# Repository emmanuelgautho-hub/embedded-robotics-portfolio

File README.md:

# embedded-robotics-portfolio
Portfolio de projets en Systèmes Embarqués, Robotique &amp; Vision IA - Emmanuel GAUTHO (ESIGELEC)
# Portfolio : Systèmes Embarqués et Robotique

Ce dépôt centralise mes principaux projets techniques et académiques. Je m'appelle Emmanuel Gautho, je suis actuellement étudiant en 2ème année de cycle ingénieur à l'ESIGELEC, spécialisé en Systèmes Embarqués. Mes travaux portent principalement sur la robotique mobile, le développement de micrologiciels (firmware) bas niveau et la vision par ordinateur.

## Projets

### Navigation de Robot Quadrupède (Deep Robotics Lite3 & ROS2)
Développement d'une stack de perception et de navigation autonome pour un robot quadrupède en environnement complexe.
* Conception et implémentation d'un système de détection d'escaliers basé sur une caméra Intel RealSense, OpenCV et YOLO.
* Traitement en temps réel des flux vidéo et de profondeur pour l'extraction des caractéristiques de l'environnement.
* Création de nœuds ROS2 personnalisés pour interfacer les données de vision avec le système de contrôle des moteurs du robot.

### Robot Mobile Autonome (MSP430)
Conception du firmware bare-metal pour un petit véhicule autonome focalisé sur l'évitement d'obstacles et le suivi de trajectoire.
* Interfaçage et traitement des signaux provenant de capteurs de distance à ultrasons.
* Gestion des actionneurs et des moteurs à courant continu via des signaux PWM et des interruptions matérielles.
* Optimisation du code C bas niveau pour fonctionner sous contraintes de ressources sur un microcontrôleur Texas Instruments MSP430G2553.

### Conception Électronique et Routage PCB (KiCad)
Réalisation complète du design matériel d'un système embarqué intégrant un microcontrôleur et plusieurs capteurs.
* Développement du schéma électronique complet et association des empreintes (footprints).
* Routage des pistes du circuit imprimé en veillant à l'intégrité des signaux et à la bonne distribution de la puissance.
* Génération des fichiers Gerber prêts pour la fabrication industrielle.

### Instrumentation de Station Météo (LabVIEW)
Développement d'une application d'acquisition et de traitement de données pour une station météo multi-capteurs.
* Acquisition en temps réel des données de capteurs de température, d'humidité et de vent.
* Traitement des signaux à l'aide de la bibliothèque NI-DAQmx pour la détection de pics et le filtrage des données.

## Compétences Techniques

* **Langages de programmation :** C, C++, Python, Java, SQL, LabVIEW
* **Systèmes et OS :** Linux Embarqué (BeagleBone), Systèmes d'Exploitation Temps Réel (RTOS)
* **Matériel et CAO :** MSP430, STM32F4, Arduino, KiCad
* **Outils de développement :** Git, GitHub, VS Code, MATLAB, Simulink, VirtualBox

## A propos du code
Ces projets font partie de mon parcours académique. Les ressources partagées ici se concentrent sur le prototypage fonctionnel et la logique algorithmique plutôt que sur une optimisation prête pour la production.

## Contact

* **Email :** emmanuelgautho@gmail.com
* **LinkedIn :**

# Embedded Systems and Robotics Portfolio

This repository serves as a technical portfolio highlighting my engineering projects. I am Emmanuel Gautho, currently a second-year engineering student at ESIGELEC specializing in Embedded Systems. My work focuses on mobile robotics, embedded firmware development, and computer vision.

## Projects

### Quadruped Robot Navigation (Deep Robotics Lite3 & ROS2)
Developed a perception and autonomous navigation stack for a quadruped robot to handle complex environments.
* Designed and implemented a stair-detection system using an Intel RealSense camera combined with YOLO and OpenCV.
* Processed real-time video and depth data streams to extract environment features.
* Created custom ROS2 nodes to interface the vision data with the robot's motion control system.

### Autonomous Mobile Robot (MSP430)
Designed the bare-metal firmware for a small autonomous vehicle focused on obstacle avoidance and path tracking.
* Interfaced and processed signals from ultrasonic distance sensors.
* Managed actuators and DC motors using PWM signals and hardware interrupts.
* Optimized low-level C code to operate efficiently within limited hardware resources on a Texas Instruments MSP430G2553 microcontroller.

### Electronic Design and PCB Routing (KiCad)
Completed the hardware design for an embedded system integrating a microcontroller and various sensors.
* Developed the full schematic diagram and mapped corresponding footprints.
* Routed the PCB tracks while ensuring signal integrity and proper power distribution.
* Generated Gerber files ready for industrial manufacturing.

### Weather Station Instrumentation (LabVIEW)
Built a data acquisition and processing application for a multi-sensor weather station.
* Acquired real-time data from temperature, humidity, and wind sensors.
* Processed signals using the NI-DAQmx library for peak detection and data filtering.

## Technical Skills

* **Programming Languages:** C, C++, Python, Java, SQL, LabVIEW
* **Systems and OS:** Embedded Linux (BeagleBone), Real-Time Operating Systems (RTOS)
* **Hardware and EDA:** MSP430, STM32F4, Arduino, KiCad
* **Development Tools:** Git, GitHub, VS Code, MATLAB, Simulink, VirtualBox

## About the Code
These projects are part of my academic learning curve. The code resources shared here focus on functional prototyping and algorithm logic rather than production-ready optimization.

## Contact

* **Email:** emmanuelgautho@gmail.com
* **LinkedIn:**

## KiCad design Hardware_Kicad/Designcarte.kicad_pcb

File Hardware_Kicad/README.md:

## ⏱️ Contexte du Projet & Objectifs
Ce projet a été réalisé en un temps limité de **6 heures** dans le cadre d'une initiation au design électronique à l'ESIGELEC. 

**Objectifs principaux :**
* Prise en main rapide et en totale autonomie du logiciel **KiCad** (découverte de l'outil).
* Saisie de schéma électronique à partir d'un cahier des charges basique (Thermometre MSP430 / LM35).
* Association des composants à leurs empreintes physiques et initiation au placement sur PCB avec génération d'un rendu 3D.

---

## 📈 Compétences Validées durant ce TP
* **Apprentissage Express :** Capacité à appréhender un nouvel outil de CAO complexe (KiCad) et à sortir un livrable visuel en moins d'une journée.
* **Placement & Encombrement :** Réflexion sur la disposition des composants (piles CR2032, afficheur) pour optimiser l'espace et respecter les contraintes mécaniques du rendu 3D.
* **Compréhension du Multiplexage :** Modélisation théorique du câblage pour l'affichage dynamique 7 segments afin d'économiser les broches du microcontrôleur.

* ### ⚠️ Erreurs de conception identifiées (Revue post-projet)
Le but de ce TP de 6 heures étant une initiation rapide à l'outil KiCad, plusieurs erreurs de conception électronique ont été volontairement ou involontairement laissées dans cette version préliminaire :

1. **Alimentation du Microcontrôleur :** Les deux piles CR2032 délivrent une tension nominale de 6V (nécessaire pour le LM35 qui requiert un minimum de 4V). Cependant, le MSP430G2553 a une tension maximale absolue de 3.6V. Dans une version finale, l'ajout d'un régulateur de tension (LDO 3.3V) est indispensable pour protéger le microcontrôleur.
2. **Filtrage (Condensateurs de découplage) :** Aucun condensateur de découplage (100nF) n'a été intégré sur les lignes d'alimentation du MSP430 et du capteur. Sans eux, le bruit généré par le multiplexage de l'afficheur perturberait grandement les mesures de l'ADC.
3. **Statut du Routage :** Pour respecter le délai imparti de 6h, seul le placement des composants et la validation de l'encombrement 3D ont été réalisés. Les connexions électriques restent à l'état de "chevelu" (ratlines) et le routage des pistes de cuivre n'est pas finalisé.

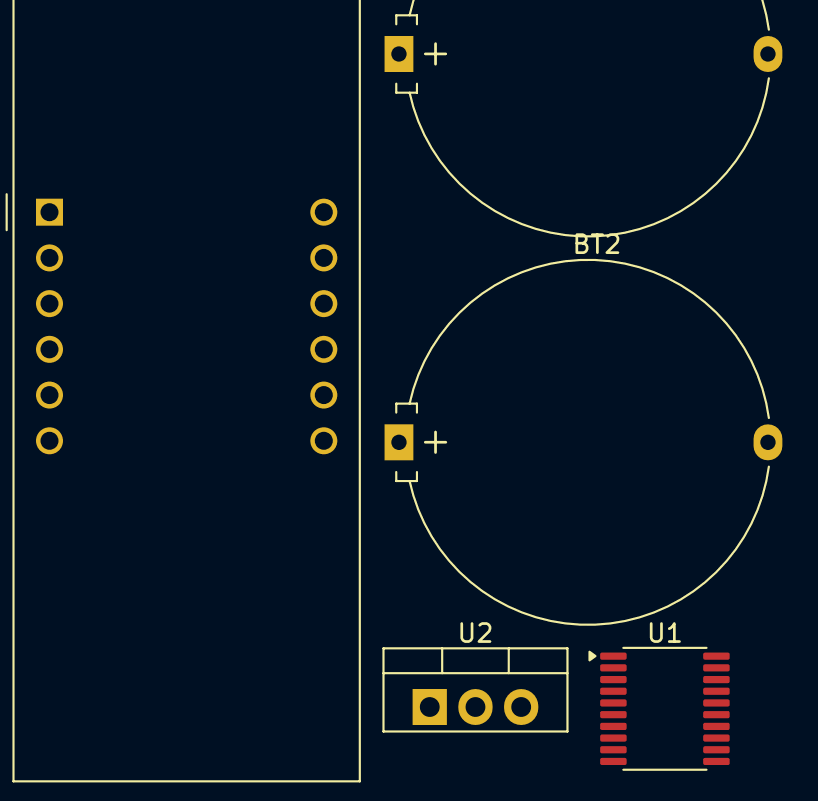
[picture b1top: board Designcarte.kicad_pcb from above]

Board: 2 copper layers, 5 parts (0 on the bottom side), 16 nets, no tracks yet.

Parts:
BT1, BT2: 3V; Battery_Panasonic_CR2032-HFN_Horizontal_CircularHoles
U1: MSP430G2553IPW20; TSSOP-20_4.4x6.5mm_P0.65mm
U2: LM35-NEB; TO-220-3_Vertical
U3: CC56-12EWA; CA56-12EWA

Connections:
unnamed: BT1.1 (+), BT2.2 (-)
unnamed: BT2.1 (+), U2.1 (+V_{S})
unnamed: U1.5 (CAOUT/VREF-/VeREF-/CA3/A3/P1.3), U3.2 (d)
unnamed: U1.20 (DVSS), U2.2 (GND)
unnamed: U1.9 (P2.1/TA1.1), U2.3 (V_{OUT})
unnamed: U1.10 (P2.2/TA1.1), U3.12 (CC1)
unnamed: U1.11 (P2.3/TA1.0), U3.9 (CC2)
unnamed: U1.12 (P2.4/TA1.2), U3.8 (CC3)
unnamed: U1.13 (P2.5/TA1.2), U3.6 (CC4)
unnamed: U1.2 (TA0CLK/ACLK/CA0/A0/P1.0), U3.11 (a)
unnamed: U1.6 (TCK/SMCLK/UCB0STE/UCA0CLK/VREF+/VeREF+/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), U3.1 (e)
unnamed: U1.14 (TDI/TCLK/UCB0SOMI/UCB0SCL/TA0.1/CA6/A6/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), U3.5 (g)
unnamed: U1.15 (TDO/TDI/UCB0SIMO/UCB0SDA/CAOUT/CA7/A7/P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), U3.3 (DPX)
unnamed: U1.7 (TMS/UCB0CLK/UCA0STE/TA0.0/CA5/A5/P1.5), U3.10 (f)
unnamed: U1.3 (UCA0RXD/UCA0SOMI/TA0.0/CA1/A1/P1.1), U3.7 (b)
unnamed: U1.4 (UCA0TXD/UCA0SIMO/TA0.1/CA2/A2/P1.2), U3.4 (c)

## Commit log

2026-05-26 Create Lite3
2026-05-26 Create lite
2026-05-26 Create todelete
2026-05-28 Rename Capture d'écran 2025-11-25 103822.png to Ihm_principale.png
2026-05-28 Rename Capture d'écran 2025-11-25 103842.png to temp_seuil.png
2026-05-28 Rename Capture d'écran 2025-11-25 103913.png to temp_scope.png
2026-05-28 Rename Capture d'écran 2025-11-25 104021.png to Girouette_scope.png
2026-05-28 Rename Capture d'écran 2025-11-25 104303.png to Gir_ihm.png
2026-05-28 Rename Capture d'écran 2025-11-25 104337.png to Anenometre_ihm.png
2026-05-28 Rename Capture d'écran 2025-11-25 104414.png to Anenometre_scope.png
2026-05-28 Rename Capture d'écran 2025-11-25 104434.png to Pluviometre_ihm.png
2026-05-28 Rename Capture d'écran 2025-11-25 104521.png to Pluviometre_scope.png
2026-05-28 Rename Capture d'écran 2025-11-25 103935.png to Compteur_ihm.png
2026-06-04 Create t
